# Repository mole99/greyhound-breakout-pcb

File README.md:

# Greyhound Breakout PCB

This repository holds the breakout PCB for [Greyhound](https://github.com/mole99/greyhound-ihp) (v1 and v2).

- `greyhound_v1/` was designed for [Greyhound v1](https://github.com/mole99/greyhound-ihp-v1) taped out on 07 Apr 2025, SG13G2.
- `greyhound_v2/` was designed for [Greyhound v2](https://github.com/mole99/greyhound-ihp-v2) taped out on 14 Sep 2025, SG13CMOS.

> [!NOTE]
> Normally, Greyhound v1 and v2 are pin compatible (and they are), but swissbit made a mistake during packaging which shifted all the bonds by one 🤦‍♂️
> See [greyhound_v2_xray](img/greyhound_v2_xray.jpg).

It is based on the [Tiny Tapeout breakout](https://github.com/TinyTapeout/breakout-pcb) board. Thanks a lot!

The PCB was designed with KiCad version 9.0.

Check out the project in your browser using KiCanvas: [Greyhound Breakout PCB](https://kicanvas.org/?github=https://github.com/mole99/greyhound-breakout-pcb/blob/main/breakout-qfn.kicad_pro)

# License

The PCB is licensed under the Apache 2 License

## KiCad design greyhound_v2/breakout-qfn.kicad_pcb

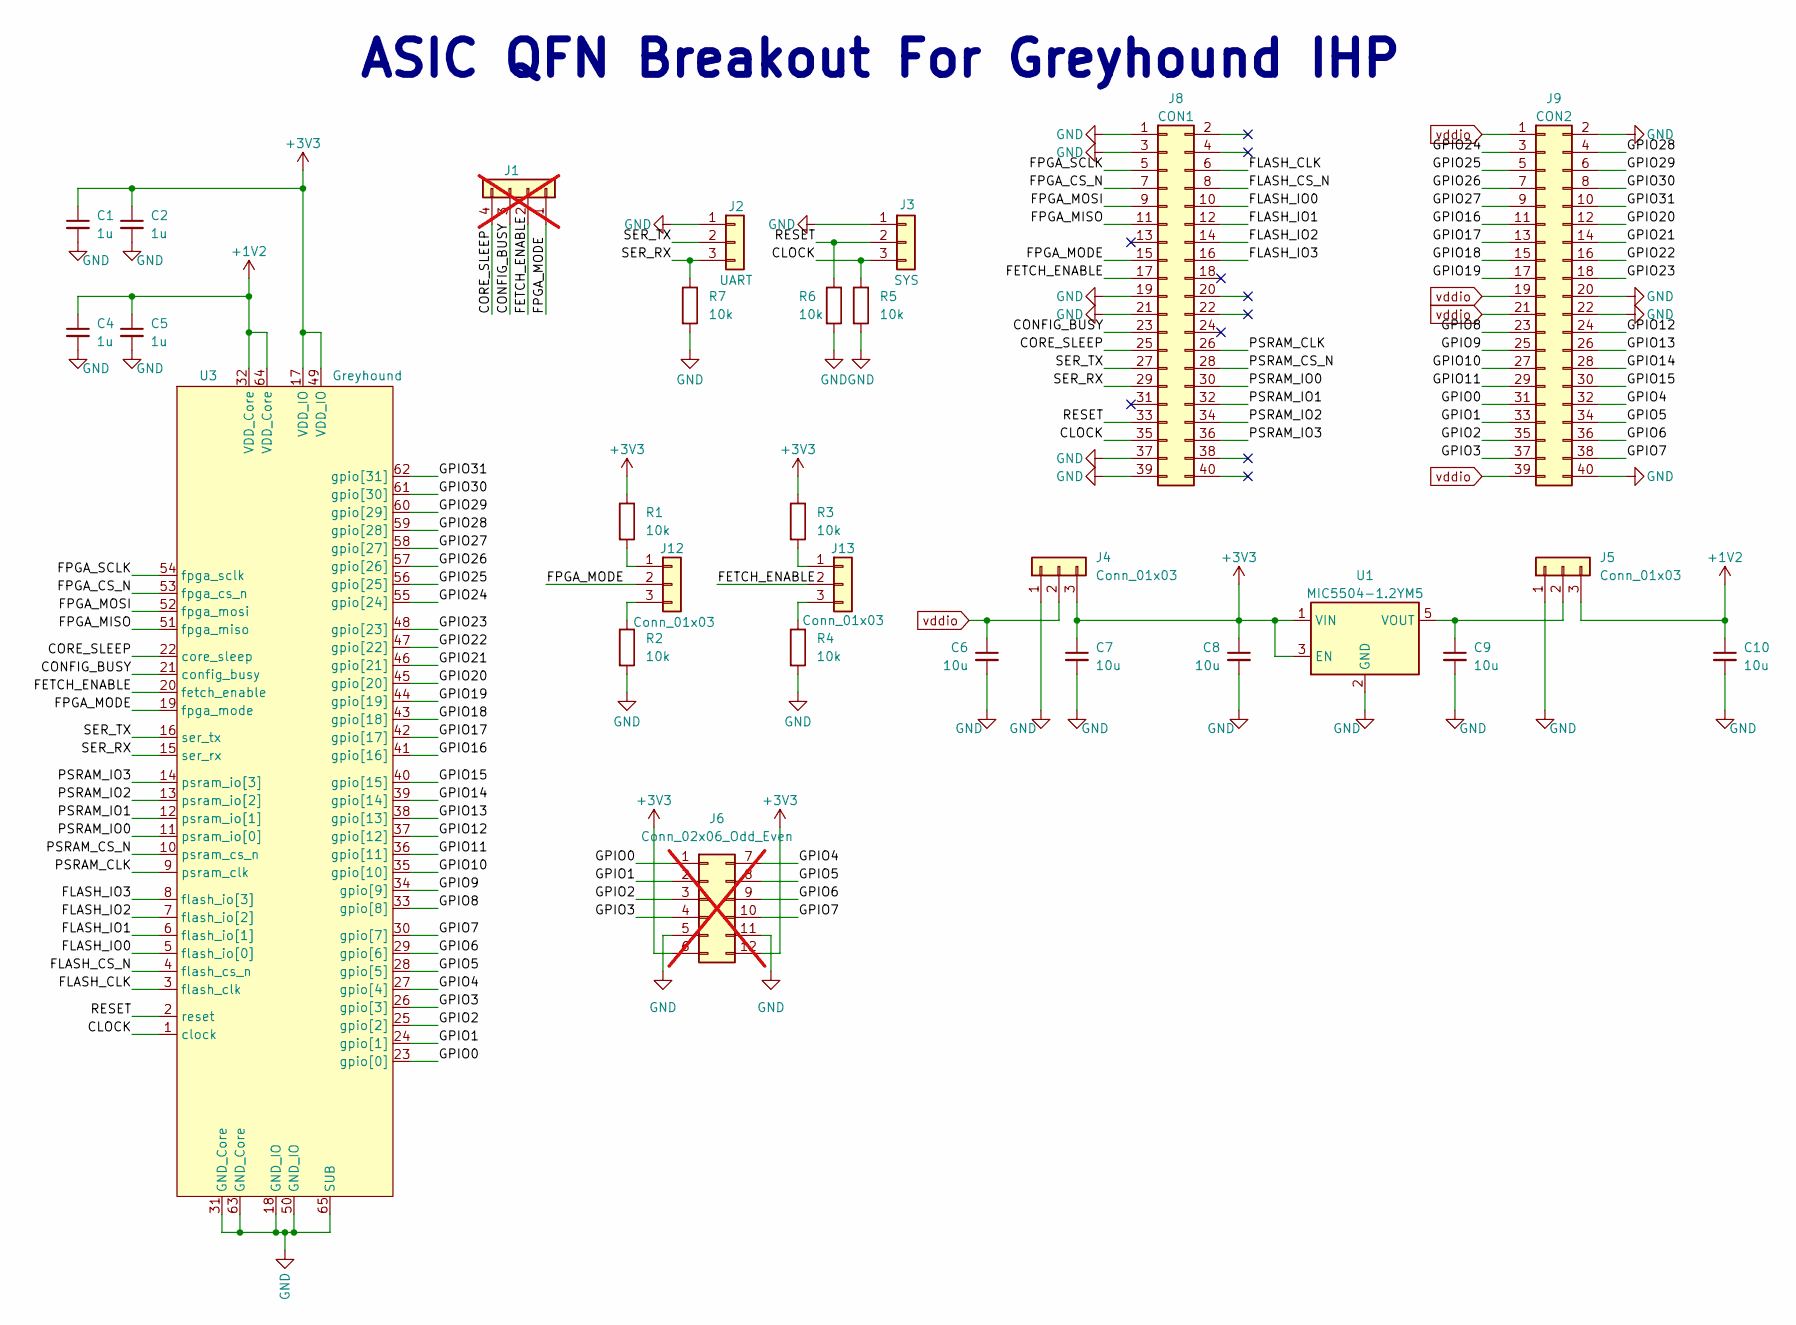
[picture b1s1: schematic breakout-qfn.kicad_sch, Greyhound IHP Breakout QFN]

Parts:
C1, C2, C4, C5: 1u; C_0402_1005Metric
C6, C7, C8, C9, C10: 10u; C_0603_1608Metric
J1: Conn_01x04; PinHeader_1x04_P2.54mm_Vertical; not fitted
J2: UART; PinHeader_1x03_P2.54mm_Vertical
J3: SYS; PinHeader_1x03_P2.54mm_Vertical
J4, J5, J12, J13: Conn_01x03; PinHeader_1x03_P2.54mm_Vertical
J6: Conn_02x06_Odd_Even; PinHeader_2x06_P2.54mm_Vertical; not fitted
J8: CON1; PinSocket_2x20_P2.54mm_Vertical
J9: CON2; PinSocket_2x20_P2.54mm_Vertical
R1, R2, R3, R4, R5, R6, R7: 10k; R_0603_1608Metric; LCSC C202394
U1: MIC5504-1.2YM5; SOT-23-5
U3: Greyhound; QFN-64-1EP_9x9mm_P0.5mm_EP4.7x4.7mm_IHP_swissbit

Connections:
+1V2: C4.1, C5.1, C10.1, J5.3, U3.32 (VDD_Core), U3.64 (VDD_Core)
+3V3: C1.1, C2.1, C7.1, C8.1, J4.3, J6.6, J6.12, R1.1, R3.1, U1.1 (VIN), U1.3 (EN), U3.17 (VDD_IO), U3.49 (VDD_IO)
/CLOCK: J3.3, J8.35, R5.1, U3.1 (clock)
/CONFIG_BUSY: J1.3, J8.23, U3.21 (config_busy)
/CORE_SLEEP: J1.4, J8.25, U3.22 (core_sleep)
/FETCH_ENABLE: J1.2, J8.17, J13.2, U3.20 (fetch_enable)
/FLASH_CLK: J8.6, U3.3 (flash_clk)
/FLASH_CS_N: J8.8, U3.4 (flash_cs_n)
/FLASH_IO0: J8.10, U3.5 (flash_io[0])
/FLASH_IO1: J8.12, U3.6 (flash_io[1])
/FLASH_IO2: J8.14, U3.7 (flash_io[2])
/FLASH_IO3: J8.16, U3.8 (flash_io[3])
/FPGA_CS_N: J8.7, U3.53 (fpga_cs_n)
/FPGA_MISO: J8.11, U3.51 (fpga_miso)
/FPGA_MODE: J1.1, J8.15, J12.2, U3.19 (fpga_mode)
/FPGA_MOSI: J8.9, U3.52 (fpga_mosi)
/FPGA_SCLK: J8.5, U3.54 (fpga_sclk)
/GPIO0: J6.1, J9.31, U3.23 (gpio[0])
/GPIO1: J6.2, J9.33, U3.24 (gpio[1])
/GPIO2: J6.3, J9.35, U3.25 (gpio[2])
/GPIO3: J6.4, J9.37, U3.26 (gpio[3])
/GPIO4: J6.7, J9.32, U3.27 (gpio[4])
/GPIO5: J6.8, J9.34, U3.28 (gpio[5])
/GPIO6: J6.9, J9.36, U3.29 (gpio[6])
/GPIO7: J6.10, J9.38, U3.30 (gpio[7])
/GPIO8: J9.23, U3.33 (gpio[8])
/GPIO9: J9.25, U3.34 (gpio[9])
/GPIO10: J9.27, U3.35 (gpio[10])
/GPIO11: J9.29, U3.36 (gpio[11])
/GPIO12: J9.24, U3.37 (gpio[12])
/GPIO13: J9.26, U3.38 (gpio[13])
/GPIO14: J9.28, U3.39 (gpio[14])
/GPIO15: J9.30, U3.40 (gpio[15])
/GPIO16: J9.11, U3.41 (gpio[16])
/GPIO17: J9.13, U3.42 (gpio[17])
/GPIO18: J9.15, U3.43 (gpio[18])
/GPIO19: J9.17, U3.44 (gpio[19])
/GPIO20: J9.12, U3.45 (gpio[20])
/GPIO21: J9.14, U3.46 (gpio[21])
/GPIO22: J9.16, U3.47 (gpio[22])
/GPIO23: J9.18, U3.48 (gpio[23])
/GPIO24: J9.3, U3.55 (gpio[24])
/GPIO25: J9.5, U3.56 (gpio[25])
/GPIO26: J9.7, U3.57 (gpio[26])
/GPIO27: J9.9, U3.58 (gpio[27])
/GPIO28: J9.4, U3.59 (gpio[28])
/GPIO29: J9.6, U3.60 (gpio[29])
/GPIO30: J9.8, U3.61 (gpio[30])
/GPIO31: J9.10, U3.62 (gpio[31])
/PSRAM_CLK: J8.26, U3.9 (psram_clk)
/PSRAM_CS_N: J8.28, U3.10 (psram_cs_n)
/PSRAM_IO0: J8.30, U3.11 (psram_io[0])
/PSRAM_IO1: J8.32, U3.12 (psram_io[1])
/PSRAM_IO2: J8.34, U3.13 (psram_io[2])
/PSRAM_IO3: J8.36, U3.14 (psram_io[3])
/RESET: J3.2, J8.33, R6.1, U3.2 (reset)
/SER_RX: J2.3, J8.29, R7.1, U3.15 (ser_rx)
/SER_TX: J2.2, J8.27, U3.16 (ser_tx)
GND: C1.2, C2.2, C4.2, C5.2, C6.2, C7.2, C8.2, C9.2, C10.2, J2.1, J3.1, J4.1, J5.1, J6.5, J6.11, J8.1, J8.3, J8.19, J8.21, J8.37, J8.39, J9.2, J9.20, J9.22, J9.40, R2.2, R4.2, R5.2, R6.2, R7.2, U1.2 (GND), U3.18 (GND_IO), U3.31 (GND_Core), U3.50 (GND_IO), U3.63 (GND_Core), U3.65 (SUB)
unnamed: C9.1, J5.2, U1.5 (VOUT)
unnamed: J12.1, R1.2
unnamed: J12.3, R2.1
unnamed: J13.1, R3.2
unnamed: J13.3, R4.1
vddio: C6.1, J4.2, J9.1, J9.19, J9.21, J9.39

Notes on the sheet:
ASIC QFN Breakout For Greyhound IHP

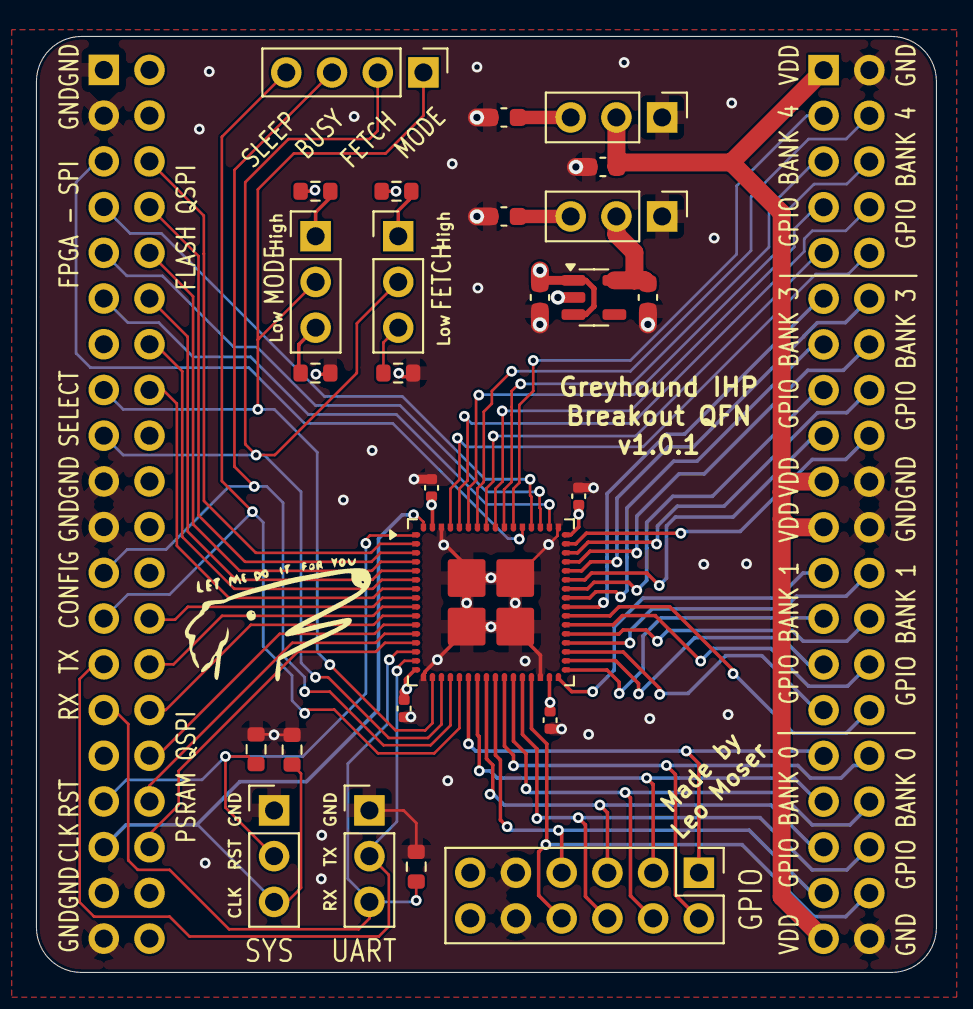
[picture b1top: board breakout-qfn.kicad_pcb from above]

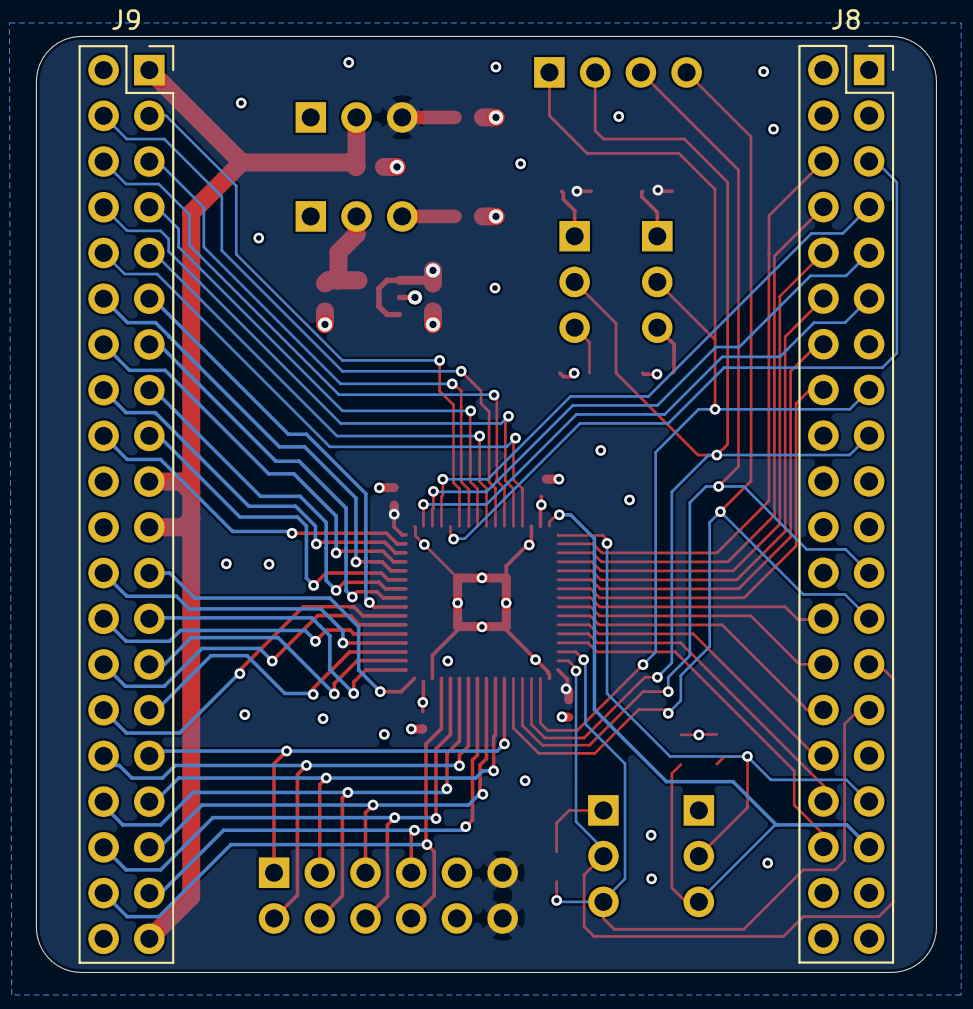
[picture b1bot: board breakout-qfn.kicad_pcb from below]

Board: 4 copper layers, 50.0 x 52.0 mm, 28 parts (2 on the bottom side), 65 nets.

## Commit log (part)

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2026-02-16 Add LICENSE
2026-02-21 Update README, add images
2026-02-21 Fix link
2026-02-21 Adjust image size
2026-02-21 Update image

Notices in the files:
breakout-qfn.kicad_sch:
(C) 2024-2025 Pat Deegan
(C) 2025 Sylvain Munaut
(C) 2026 Leo Moser
